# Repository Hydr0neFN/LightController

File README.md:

# LightController

ESP32-C3 Super Mini based LED controller with USB-C PD input, DC barrel jack/ terminal block input, two PWM-dimmed LED strip channels, and an addressable NeoPixel output. Apple HomeKit native via [HomeSpan](https://github.com/HomeSpan/HomeSpan), with optional MQTT status reporting.

Built as a one-person project for **Year 1 Period 4 — Power up Yourself** at Hanze University of Applied Sciences, Groningen.

## Hardware

Custom PCB designed in KiCad (design files in [`pcb/`](pcb/)).

### Key Components

| Component | Role |
|---|---|
| ESP32-C3 Super Mini | MCU, WiFi, HomeKit bridge |
| CH224K | USB-C PD sink controller (5V/9V/12V/15V/20V negotiation) |
| AP63205WU | Buck converter, PD/DC rail → 5V for MCU |
| SN74LVC1T45 | 3.3V → 5V level shifter for NeoPixel DIN |
| IRFZ44N × 2 | Low-side N-MOSFETs for LED strip channels |
| UCC27423 | Dual gate driver for MOSFET channels |

### Power Input (Up to 24V tolorance)

- **USB-C PD** via CH224K — negotiates 5V/9V/12V/15V/20V from a PD source
- **DC barrel jack** — direct input (e.g. 12/24V wall adapter), bypasses PD negotiation
- **Terminal Block** — direct input if user have PSU input, bypasses PD negotiation.

Three inputs feed the LED strips directly and the AP63205 buck for 5V MCU power.

### Outputs (All shares same power rail)

- **Channel A** — PWM-dimmed LED strip (low-side MOSFET, enable gate)
- **Channel B** — PWM-dimmed LED strip (low-side MOSFET, enable gate)
- **NeoPixel** — addressable RGB string via level-shifted DIN (SN74LVC1T45)

### PCB History

The PCB was originally designed by [Andrei (ihoneypot)](https://github.com/ihoneypot) as a basic LED controller. I modified the design to add:

- USB-C PD input with CH224K voltage negotiation
- DC barrel jack input as alternative power source
- ESP8266 → ESP32-C3 Super Mini swap (HomeKit-capable, smaller footprint)
- Unified power routing: three input paths merged to one rail, split to two LED strip outputs + NeoPixel output
- 3.3V→5V level shifter for NeoPixel data line

### PD Status — Not Working

The CH224K PD negotiation circuit is **currently disabled** (`ENABLE_PD 0` in config). During bringup we burned several CH224K chips and discovered through debugging:

- The 1kΩ resistor from VBUS to VDD acts as a voltage divider but the 0805 package cannot dissipate the power at higher voltages (P = V²/R; at 20V that's 0.4W through a 0.1W-rated resistor — it overheats and eventually burns)
- USB-C D+/D- must be shorted on the chip side for proper enumeration
- The USB-C connector requires careful reflow; loose joints cause intermittent communication

**Fixes needed for a future revision:**
- Use a power resistor rated for ≥0.4W (or ≥0.15W if limiting to 12V max)
- Short D+/D- on the CH224K side, remove the data line routing from the USB-C connector
- The firmware PD controller (`PDController.h`) is implemented but untested on hardware — only the hardware needs fixing before end-to-end testing can happen

## Firmware

PlatformIO project targeting `nologo_esp32c3_super_mini` via the [pioarduino](https://github.com/pioarduino/platform-espressif32) fork (arduino-esp32 core 3.3.9, ESP-IDF 5.5.4).

### Features

- **HomeKit native** — two dimmable lightbulbs (CH A/B) + one RGB lightbulb (NeoPixel), bridged accessory
- **PD voltage switching** — load-shedding before rail transition, NVS persistence for brown-out recovery (disabled until hardware fix)
- **MQTT status** — periodic JSON status publish, network voltage control via `lightctrl/cmd/voltage`
- **Web Log** — live status/log at `http://<device-ip>/status`
- **Serial CLI** — `V0`..`V4` for PD voltage, `J` for status JSON, plus full HomeSpan command set
- **OTA updates** — via HomeSpan's built-in OTA

### Building

1. Copy `src/config.h.example` → `src/config.h`
2. Edit `config.h` — set your WiFi credentials, HomeKit pairing code, MQTT broker IP, and NeoPixel count
3. Build and flash:

```bash
pio run -t upload
pio device monitor
```

### Pin Map

| GPIO | Function |
|---|---|
| 0 | CH B PWM (strapping pin) |
| 1 | CH A PWM |
| 2 | CH A enable |
| 3 | CH B enable |
| 4 | NeoPixel DIN |
| 5 | CH224K CFG1 |
| 6 | CH224K CFG3 |
| 7 | CH224K CFG2 |
| 8 | Status LED (boot strapping) |
| 21 | CH224K PG (Power Good) |

### Project Structure

```
├── src/
│   ├── main.cpp           # Setup, loop, serial commands, status LED
│   ├── config.h.example   # Configuration template (copy to config.h)
│   ├── Lights.h           # DimmableChannel + NeoStrip HomeKit services
│   ├── PDController.h     # CH224K PD voltage negotiation driver
│   └── StatusReporter.h   # MQTT publisher + JSON status builder
├── pcb/                   # KiCad 10 design files
│   ├── LEDController.kicad_sch   # Schematic
│   ├── LEDController.kicad_pcb   # PCB layout
│   ├── LEDController.kicad_pro   # Project file
│   ├── LEDController.csv         # BOM
│   ├── LEDController.pretty/     # Custom footprints (ESP32-C3 module, UCC27423)
│   ├── LedPannel.pretty/        # Custom footprints (PowerDI diode, inductor)
│   └── Prod/                    # Production Gerber files
└── platformio.ini
```

## Dependencies

| Library | Version | Purpose |
|---|---|---|
| [HomeSpan](https://github.com/HomeSpan/HomeSpan) | ≥2.1.0 | HomeKit accessory framework |
| [PubSubClient](https://github.com/knolleary/pubsubclient) | ≥2.8 | MQTT client |

## Credits

- **PCB base design** — [Andrei (ihoneypot)](https://github.com/ihoneypot)
- **Modifications, firmware, bringup** — [Yu-I (Hydr0neFN)](https://github.com/Hydr0neFN)

## License

MIT

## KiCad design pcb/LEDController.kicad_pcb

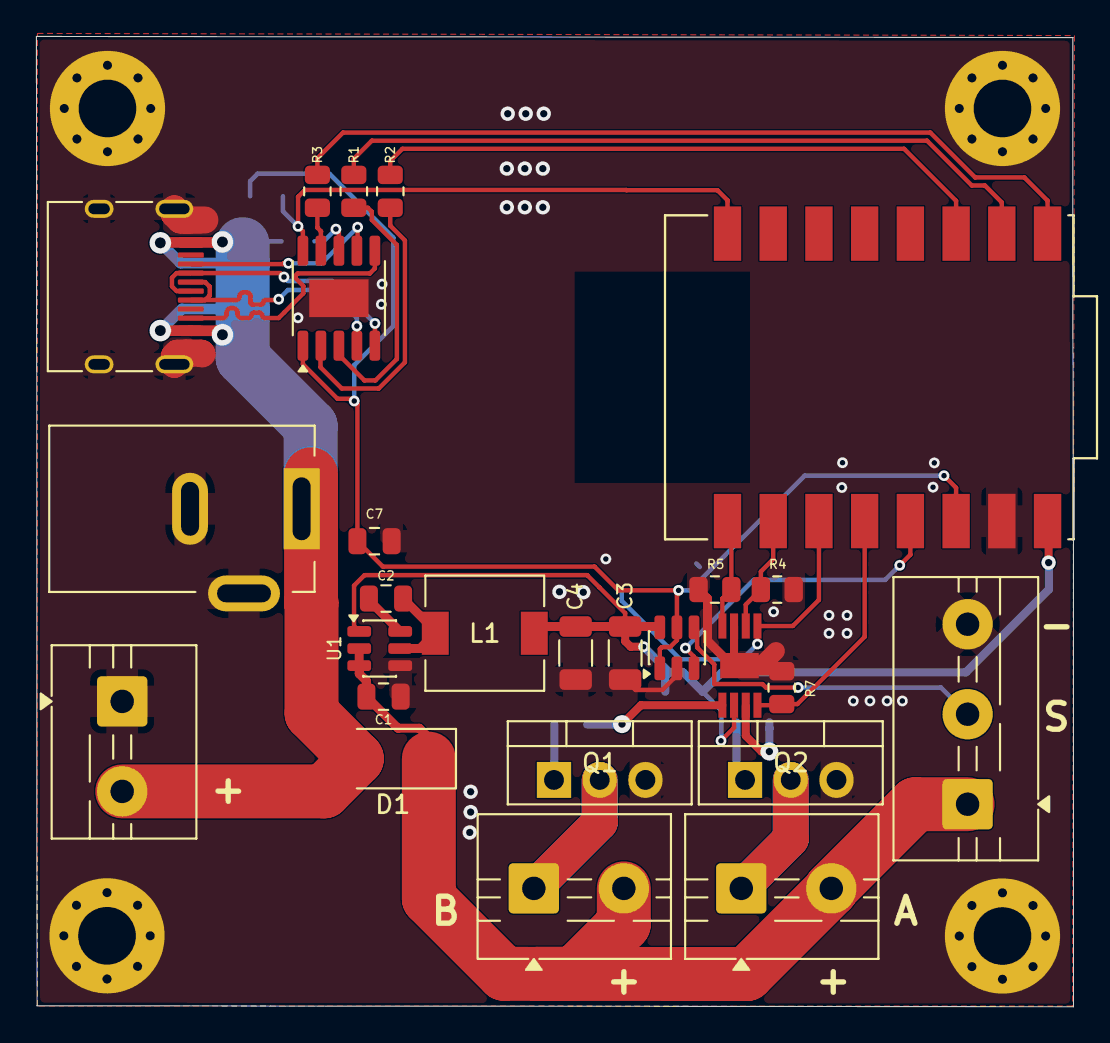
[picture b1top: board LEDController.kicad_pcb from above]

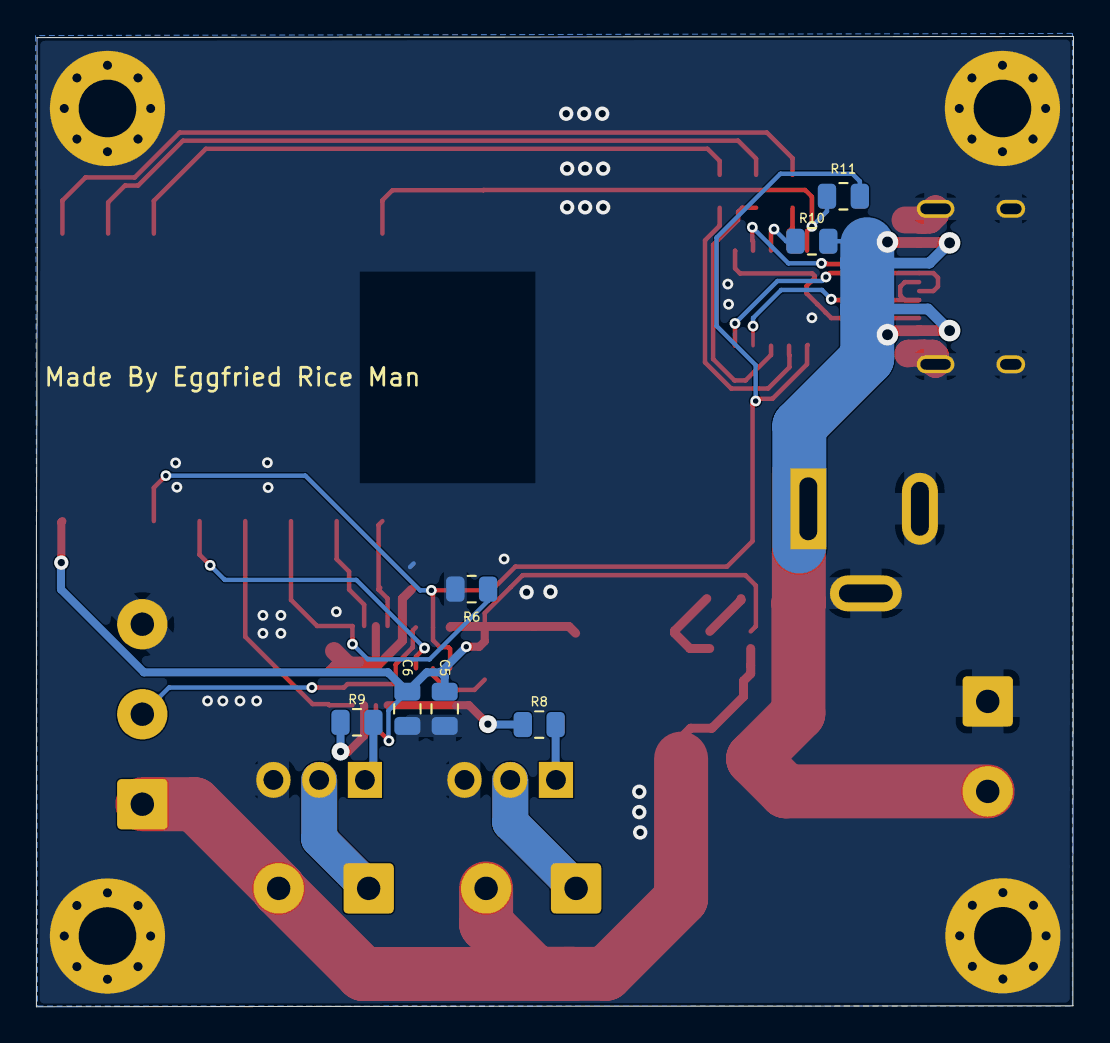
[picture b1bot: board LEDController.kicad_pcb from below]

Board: 2 copper layers, 57.6 x 53.9 mm, 37 parts (7 on the bottom side), 31 nets.

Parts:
C1: C10µF; C_0805_2012Metric
C2: C100nF; C_0805_2012Metric
C3, C4: C22µF; C_1206_3216Metric
C5, C6: 10uF; C_0805_2012Metric
C7: 1uF; C_0805_2012Metric
D1: SS54; D_SMA
H1, H2, H3, H4: MountingHole_Pad; MountingHole_3.2mm_M3_Pad_Via
J1: USB_C_Receptacle; USB_C_Receptacle_HRO_TYPE-C-31-M-12
J2: Barrel_Jack_Switch_MountingPin; BarrelJack_Kycon_KLDX-0202-xC_Horizontal
J3, J4, J5: Screw_Terminal_01x02; TerminalBlock_MaiXu_MX126-5.0-02P_1x02_P5.00mm
J6: Screw_Terminal_01x03; TerminalBlock_MaiXu_MX126-5.0-03P_1x03_P5.00mm
L1: L4.7µH; L_6.3x6.3_H3
Q1, Q2: IRFZ44N; TO-220-3_Vertical
R1, R2, R3: R1K; R_0805_2012Metric
R4, R5, R6, R7, R8, R9, R10, R11: 10K; R_0805_2012Metric
U1: AP63205WU; TSOT-23-6
U2: ESP32-C3_SUPERMINI_SMD; MODULE_ESP32-C3_SUPERMINI_SMD
U3: CH224K; SSOP-10-1EP_3.9x4.9mm_P1mm_EP2.1x3.3mm
U4: UCC2742x
U5: SN74LVC1T45DBV; SOT-23-6

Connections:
+3.3V: C7.1, R11.2, U2.3.3 (3V3), U3.1 (VDD), U5.1 (VCCA), U5.5 (DIR)
+5V: C3.2, C4.2, C5.1, C6.1, L1.2, U1.1 (FB), U2.5V, U4.6 (VDD), U5.6 (VCCB)
/CFG1: R3.2, U3.9 (CFG1)
/CFG2: R2.2, U3.2 (CFG2)
/CFG3: R1.2, U3.3 (CFG3)
/ENBA: R6.2, U2.2 (GPIO2), U4.1 (ENBA)
/ENBB: R7.2, U2.3 (GPIO3), U4.8 (ENBB)
/PG: R11.1, U2.21 (GPIO21), U3.10 (PG)
/USB_CC1: J1.A5 (CC1), U3.7 (CC1)
/USB_CC2: J1.B5 (CC2), U3.6 (CC2)
/USB_D+: J1.A6 (D+), J1.B6 (D+), U3.4 (DP)
/USB_D-: J1.A7 (D-), J1.B7 (D-), U3.5 (DM)
/VBUS_PD: D1.2 (A), J1.A4 (VBUS), J1.A9 (VBUS), J1.B4 (VBUS), J1.B9 (VBUS), J2.1, J3.2, R10.2
/VIN: C1.1, D1.1 (K), J4.2, J5.2, J6.1, U1.2 (EN), U1.3 (IN)
DRAINA: J4.1, Q2.2 (D)
DRAINB: J5.1, Q1.2 (D)
GATEA: Q2.1 (G), R9.2
GATEB: Q1.1 (G), R8.2
GND: C1.2, C3.1, C4.1, C5.2, C6.2, C7.2, H1.1 (1_1), H2.1 (1_1), H3.1 (1_1), H4.1 (1_1), J1.A1 (GND), J1.A12 (GND), J1.B1 (GND), J1.B12 (GND), J1.SH (SHIELD), J2.2, J2.3, J3.1, J6.3, Q1.3 (S), Q2.3 (S), R4.1, R5.2, R6.1, R7.1, U1.4 (GND), U2.G (GND), U3.11 (GND), U4.3 (GND), U4.9, U5.2 (GND)
NEOPIXEL_DIN: U2.4 (GPIO4), U5.3 (A)
NEO_5V_DIN: J6.2, U5.4 (B)
unnamed: C2.2, U1.6 (BST)
unnamed: C2.1, L1.1, U1.5 (SW)
unnamed: R3.1, U2.5 (GPIO5)
unnamed: R1.1, U2.6 (GPIO6)
unnamed: R2.1, U2.7 (GPIO7)
unnamed: R10.1, U3.8 (VBUS)
unnamed: R9.1, U4.7 (OUTA)
unnamed: R8.1, U4.5 (OUTB)
PWM1: R4.2, U2.1 (GPIO1), U4.2 (INA)
PWM2: R5.1, U2.0 (GPIO0), U4.4 (INB)

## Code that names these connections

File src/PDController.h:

#pragma once
#include <Arduino.h>
#include <Preferences.h>
#include "config.h"

// ============================================================================
//  CH224K USB-PD sink controller
//
//  CFG truth table (requested voltage), CFG bit meaning: 1 = high, 0 = low.
//    5V : CFG1=1  CFG2=x  CFG3=x
//    9V : CFG1=0  CFG2=0  CFG3=0
//    12V: CFG1=0  CFG2=0  CFG3=1
//    15V: CFG1=0  CFG2=1  CFG3=1
//    20V: CFG1=0  CFG2=1  CFG3=0
//
//  Wiring: each CFG line is GPIO -> 1k -> CH224K, no external pull resistors.
//  Drive convention: push-pull through the 1k series, "1" = HIGH, "0" = LOW.
//  Active drive is used (rather than high-Z) because the lines have no external
//  pull; the 1k limits current into the CH224K CFG inputs.
//
//  PG (Power Good): open-drain, active LOW. LOW => requested rail is present.
// ============================================================================

enum PDVoltage : uint8_t { PD_5V = 0, PD_9V = 1, PD_12V = 2, PD_15V = 3, PD_20V = 4 };

class PDController {
public:
  static constexpr bool enabled() { return ENABLE_PD; }

  void begin() {
    if (!enabled()) {
      // DC-only: leave CFG pins high-impedance, don't touch the CH224K, and
      // skip PG (no PD source => PG would float and read as a fault).
      pinMode(PIN_CFG1, INPUT);
      pinMode(PIN_CFG2, INPUT);
      pinMode(PIN_CFG3, INPUT);
      return;
    }

    pinMode(PIN_PG, INPUT_PULLUP);  // external 10k pull-up already present

    _prefs.begin("pd", false);
#if PD_FORCE_DEFAULT
    // Hard override: always boot at the compile-time constant.
    _current = (PDVoltage)PD_DEFAULT_VOLTAGE;
    _prefs.putUChar("volt", (uint8_t)_current);
#else
    // Restore last requested voltage (survives a brown-out reset mid-switch).
    _current = (PDVoltage)_prefs.getUChar("volt", (uint8_t)PD_DEFAULT_VOLTAGE);
#endif
    applyCfg(_current);
  }

  PDVoltage current() const { return _current; }

  // PG is active LOW. In DC-only mode there is no PD source, so report "good"
  // unconditionally (prevents a false fault on the status LED / status JSON).
  bool powerGood() const {
    if (!enabled()) return true;
    return digitalRead(PIN_PG) == LOW;
  }

  // Request a new voltage. Persists FIRST so a transient reset recovers to the
  // intended rail. Returns true if PG asserted within PD_PG_TIMEOUT_MS.
  // NOTE: caller should drop the LED loads (EN low) before calling, to ease the
  // transient on the shared 5V buck. See main.cpp setVoltageCmd().
  bool setVoltage(PDVoltage v) {
    if (!enabled()) return true;           // DC-only: no-op
    _prefs.putUChar("volt", (uint8_t)v);   // persist before touching the rail
    applyCfg(v);
    _current = v;
    return waitPowerGood(PD_PG_TIMEOUT_MS);
  }

  bool waitPowerGood(uint32_t timeoutMs) {
    uint32_t t0 = millis();
    while (!powerGood()) {
      if (millis() - t0 > timeoutMs) return false;
      delay(2);
    }
    return true;
  }

  static const char *voltageName(PDVoltage v) {
    switch (v) {
      case PD_5V:  return "5V";
      case PD_9V:  return "9V";
      case PD_12V: return "12V";
      case PD_15V: return "15V";
      case PD_20V: return "20V";
    }
    return "?";
  }

  // Approximate nominal millivolts, for status reporting.
  static uint32_t voltageMilliVolts(PDVoltage v) {
    switch (v) {
      case PD_5V:  return 5000;
      case PD_9V:  return 9000;
      case PD_12V: return 12000;
      case PD_15V: return 15000;
      case PD_20V: return 20000;
    }
    return 0;
  }

private:
  // Set CFG pins for the requested voltage (1 = float high, 0 = drive low).
  void applyCfg(PDVoltage v) {
    uint8_t c1, c2, c3;
    switch (v) {
      case PD_5V:  c1 = 1; c2 = 1; c3 = 1; break;  // CFG2/3 are don't-care -> float
      case PD_9V:  c1 = 0; c2 = 0; c3 = 0; break;
      case PD_12V: c1 = 0; c2 = 0; c3 = 1; break;
      case PD_15V: c1 = 0; c2 = 1; c3 = 1; break;
      case PD_20V: c1 = 0; c2 = 1; c3 = 0; break;
      default:     c1 = 1; c2 = 1; c3 = 1; break;  // safest fallback -> 5V
    }
    cfgWrite(PIN_CFG1, c1);
    cfgWrite(PIN_CFG2, c2);
    cfgWrite(PIN_CFG3, c3);
  }

  // CFG1..3 are GPIO -> 1k -> CH224K with no external pull resistors.
  // Drive push-pull through the 1k series: bit==1 -> HIGH, bit==0 -> LOW.
  // Active drive (not high-Z) gives a deterministic level on lines that have no
  // external pull; the 1k limits current into the CH224K CFG inputs.
  static void cfgWrite(uint8_t pin, uint8_t bit) {
    pinMode(pin, OUTPUT);
    digitalWrite(pin, bit ? HIGH : LOW);
  }

  Preferences _prefs;
  PDVoltage   _current = PD_DEFAULT_VOLTAGE;
};
